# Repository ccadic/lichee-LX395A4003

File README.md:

# lichee-LX395A4003
Converter from lichee pi zero to LX395A4003

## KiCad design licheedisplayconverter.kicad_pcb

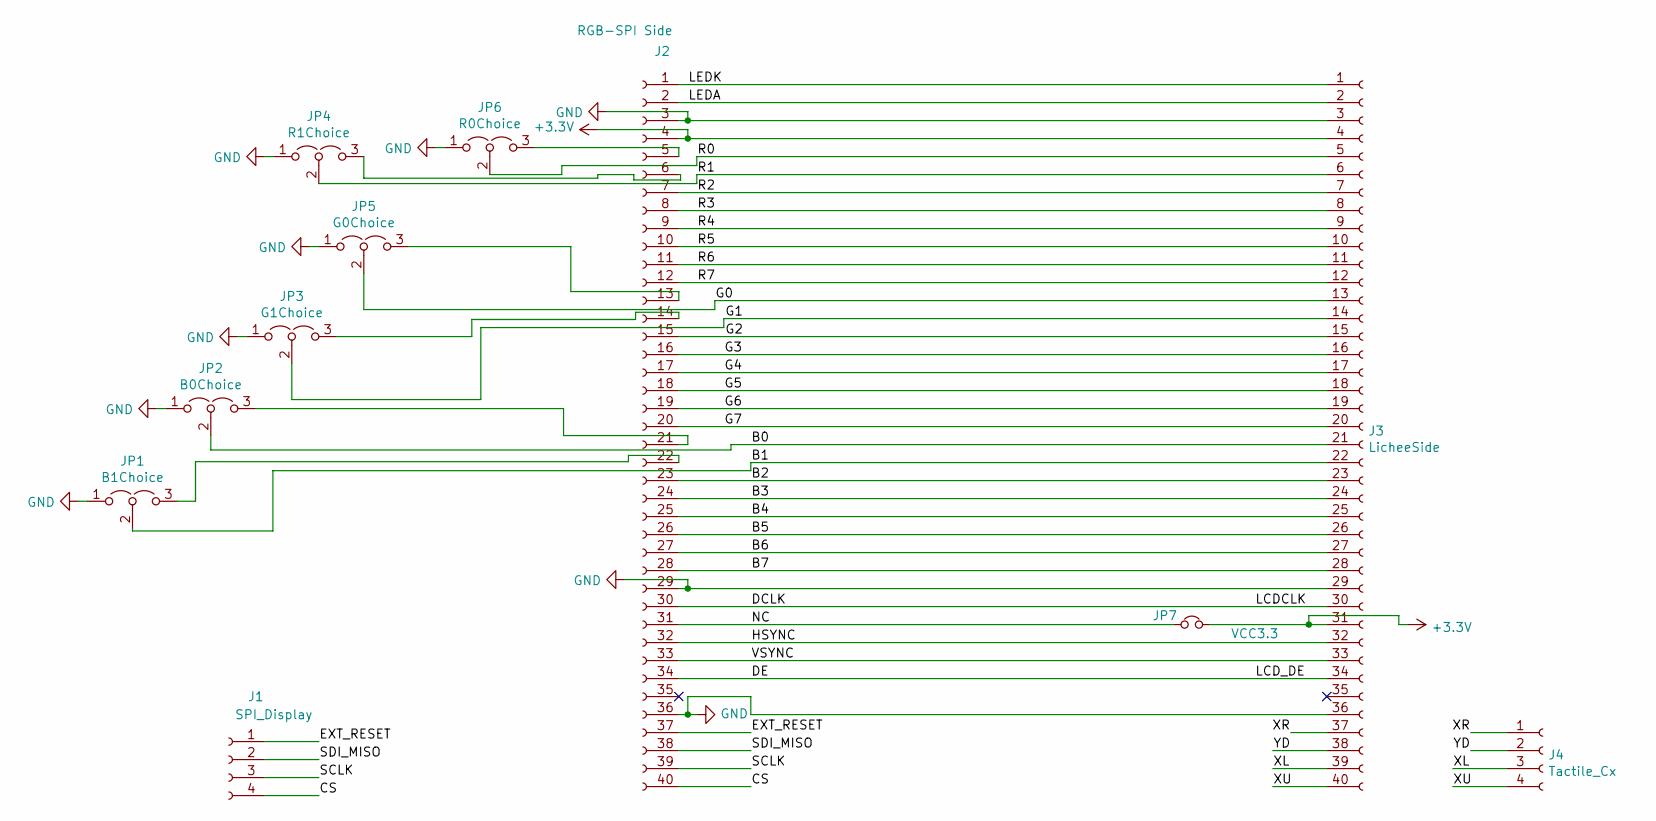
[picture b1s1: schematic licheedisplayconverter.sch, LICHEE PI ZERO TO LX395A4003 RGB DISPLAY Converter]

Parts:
J1: SPI_Display; 4padsfree
J2: RGB-SPI Side; Hirose_FH12-40S-0.5SH_1x40-1MP_P0.50mm_Horizontal
J3: LicheeSide; Hirose_FH12-40S-0.5SH_1x40-1MP_P0.50mm_Horizontal
J4: Tactile_Cx; 4padsfree
JP1: B1Choice; SolderJumper-3_P1.3mm_Open_Pad1.0x1.5mm
JP2: B0Choice; SolderJumper-3_P1.3mm_Open_Pad1.0x1.5mm
JP3: G1Choice; SolderJumper-3_P1.3mm_Open_Pad1.0x1.5mm
JP4: R1Choice; SolderJumper-3_P1.3mm_Open_Pad1.0x1.5mm
JP5: G0Choice; SolderJumper-3_P1.3mm_Open_Pad1.0x1.5mm
JP6: R0Choice; SolderJumper-3_P1.3mm_Open_Pad1.0x1.5mm
JP7: VCC3.3; SolderJumper-2_P1.3mm_Open_Pad1.0x1.5mm

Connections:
+3V3: J2.4, J3.4, J3.31, JP7.2
/B0: J3.21, JP2.2 (C)
/B1: J3.22, JP1.2 (C)
/B2: J2.23, J3.23
/B3: J2.24, J3.24
/B4: J2.25, J3.25
/B5: J2.26, J3.26
/B6: J2.27, J3.27
/B7: J2.28, J3.28
/CS: J1.4, J2.40
/DCLK: J2.30, J3.30
/DE: J2.34, J3.34
/EXT_RESET: J1.1, J2.37
/G0: J3.13, JP5.2 (C)
/G1: J3.14, JP3.2 (C)
/G2: J2.15, J3.15
/G3: J2.16, J3.16
/G4: J2.17, J3.17
/G5: J2.18, J3.18
/G6: J2.19, J3.19
/G7: J2.20, J3.20
/HSYNC: J2.32, J3.32
/LEDA: J2.2, J3.2
/LEDK: J2.1, J3.1
/NC: J2.31, JP7.1
/R0: J3.5, JP6.2 (C)
/R1: J3.6, JP4.2 (C)
/R2: J2.7, J3.7
/R3: J2.8, J3.8
/R4: J2.9, J3.9
/R5: J2.10, J3.10
/R6: J2.11, J3.11
/R7: J2.12, J3.12
/SCLK: J1.3, J2.39
/SDI_MISO: J1.2, J2.38
/VSYNC: J2.33, J3.33
/XL: J3.39, J4.3
/XR: J3.37, J4.1
/XU: J3.40, J4.4
/YD: J3.38, J4.2
GND: J2.3, J2.29, J2.36, J3.3, J3.29, J3.36, JP1.1 (A), JP2.1 (A), JP3.1 (A), JP4.1 (A), JP5.1 (A), JP6.1 (A)
unnamed: J2.5, JP6.3 (B)
unnamed: J2.6, JP4.3 (B)
unnamed: J2.13, JP5.3 (B)
unnamed: J2.14, JP3.3 (B)
unnamed: J2.21, JP2.3 (B)
unnamed: J2.22, JP1.3 (B)

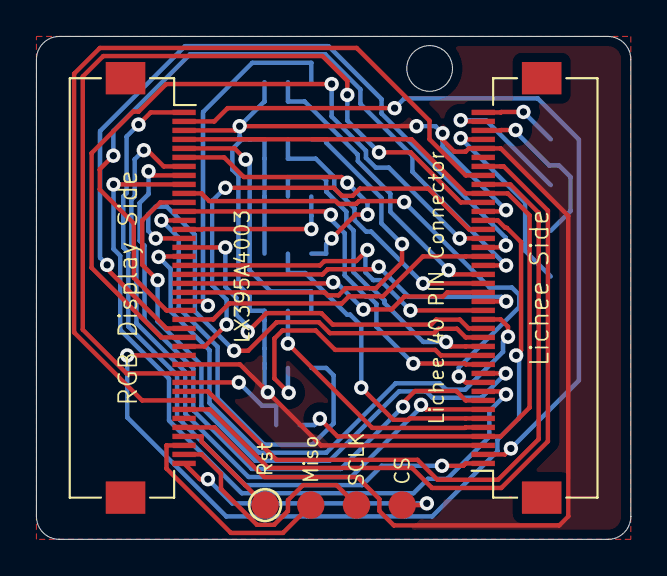
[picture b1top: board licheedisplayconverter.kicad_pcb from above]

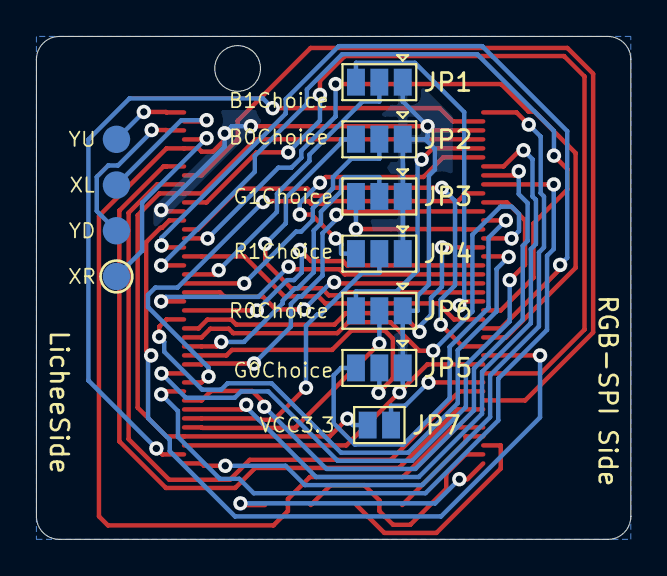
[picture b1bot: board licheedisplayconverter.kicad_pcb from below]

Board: 2 copper layers, 33.0 x 27.9 mm, 11 parts (8 on the bottom side), 47 nets.
